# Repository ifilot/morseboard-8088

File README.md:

## MorseBoard 8088

**A single-board computer built around the Intel 8088 microprocessor.**

The name **MorseBoard** is a tribute to [Stephen P.
Morse](https://en.wikipedia.org/wiki/Stephen_P._Morse), the lead architect of
the Intel 8086 microprocessor — the foundational design on which the 8088 is
based. His work played a pivotal role in shaping early x86 computing.

## Board Layout

The 8088's 20-bit address bus allows access to **1 MiB** of addressable memory,
divided into:

- **512 KiB of RAM** in the lower memory segment  
- **512 KiB of ROM** in the upper memory segment  

Address/data multiplexing is handled using **74HCT573 latches**.  
Serial communication is enabled via a **TL16C550 UART** and a **MAX232** level
shifter.

Eight LEDs are connected to **I/O port `0x00`** using a **74HCT273 register**,
providing simple visual output.

A **7.3728 MHz CAN oscillator** is used to drive both the 8088 and the serial
interface. Because of this frequency, you must use the **8088-2** variant, which
supports higher clock rates.

## Design Files

- **PCB layout**: `pcb/morseboard-8088`  
- **Firmware source**: `src/uartboard`  

Assembly is done using the [NASM assembler](https://www.nasm.us/), available via
common Linux package managers (e.g., Ubuntu). A `Makefile` is provided for
convenience.

To flash the ROM, the recommended tool is the [PICO-SST39SF0x0
programmer](https://github.com/ifilot/pico-sst39sf0x0-programmer).

## Assembly instructions

To assemble the source code of the ROM, follow the instructions below. Make sure
you have installed the proper toolchain.

``` bash
sudo apt install nasm make
```

Go to the folder and run `make`

```bash
cd src/uartboard
make
```
Flash the resulting `rom.bin` onto the SST39SF040 chip.

## Test Board

In addition to the full-featured board with UART support, a **CPU test board**
is available under `pcb/cpu-testboard`. This board is designed to validate 8088
chips — particularly useful given the unreliability of some second-hand CPUs,
since they are no longer in production.

## License

### Hardware

The hardware design files for the MorseBoard 8088 are licensed under the  
**CERN Open Hardware License v2 - Strongly Reciprocal (CERN-OHL-S-2.0)**.  
You are free to use, modify, and distribute the hardware under the terms of this
license.  
More info: [CERN-OHL-S-2.0](https://ohwr.org/project/cernohl/wikis/Documents/CERN-OHL-version-2)

### Software

The firmware and software source code is licensed under the  
**GNU General Public License v3.0 (GPLv3)**.  
You are free to use, share, and modify the code as long as derivative works
remain under the same license.  
More info: [GPLv3 License](https://www.gnu.org/licenses/gpl-3.0.html)

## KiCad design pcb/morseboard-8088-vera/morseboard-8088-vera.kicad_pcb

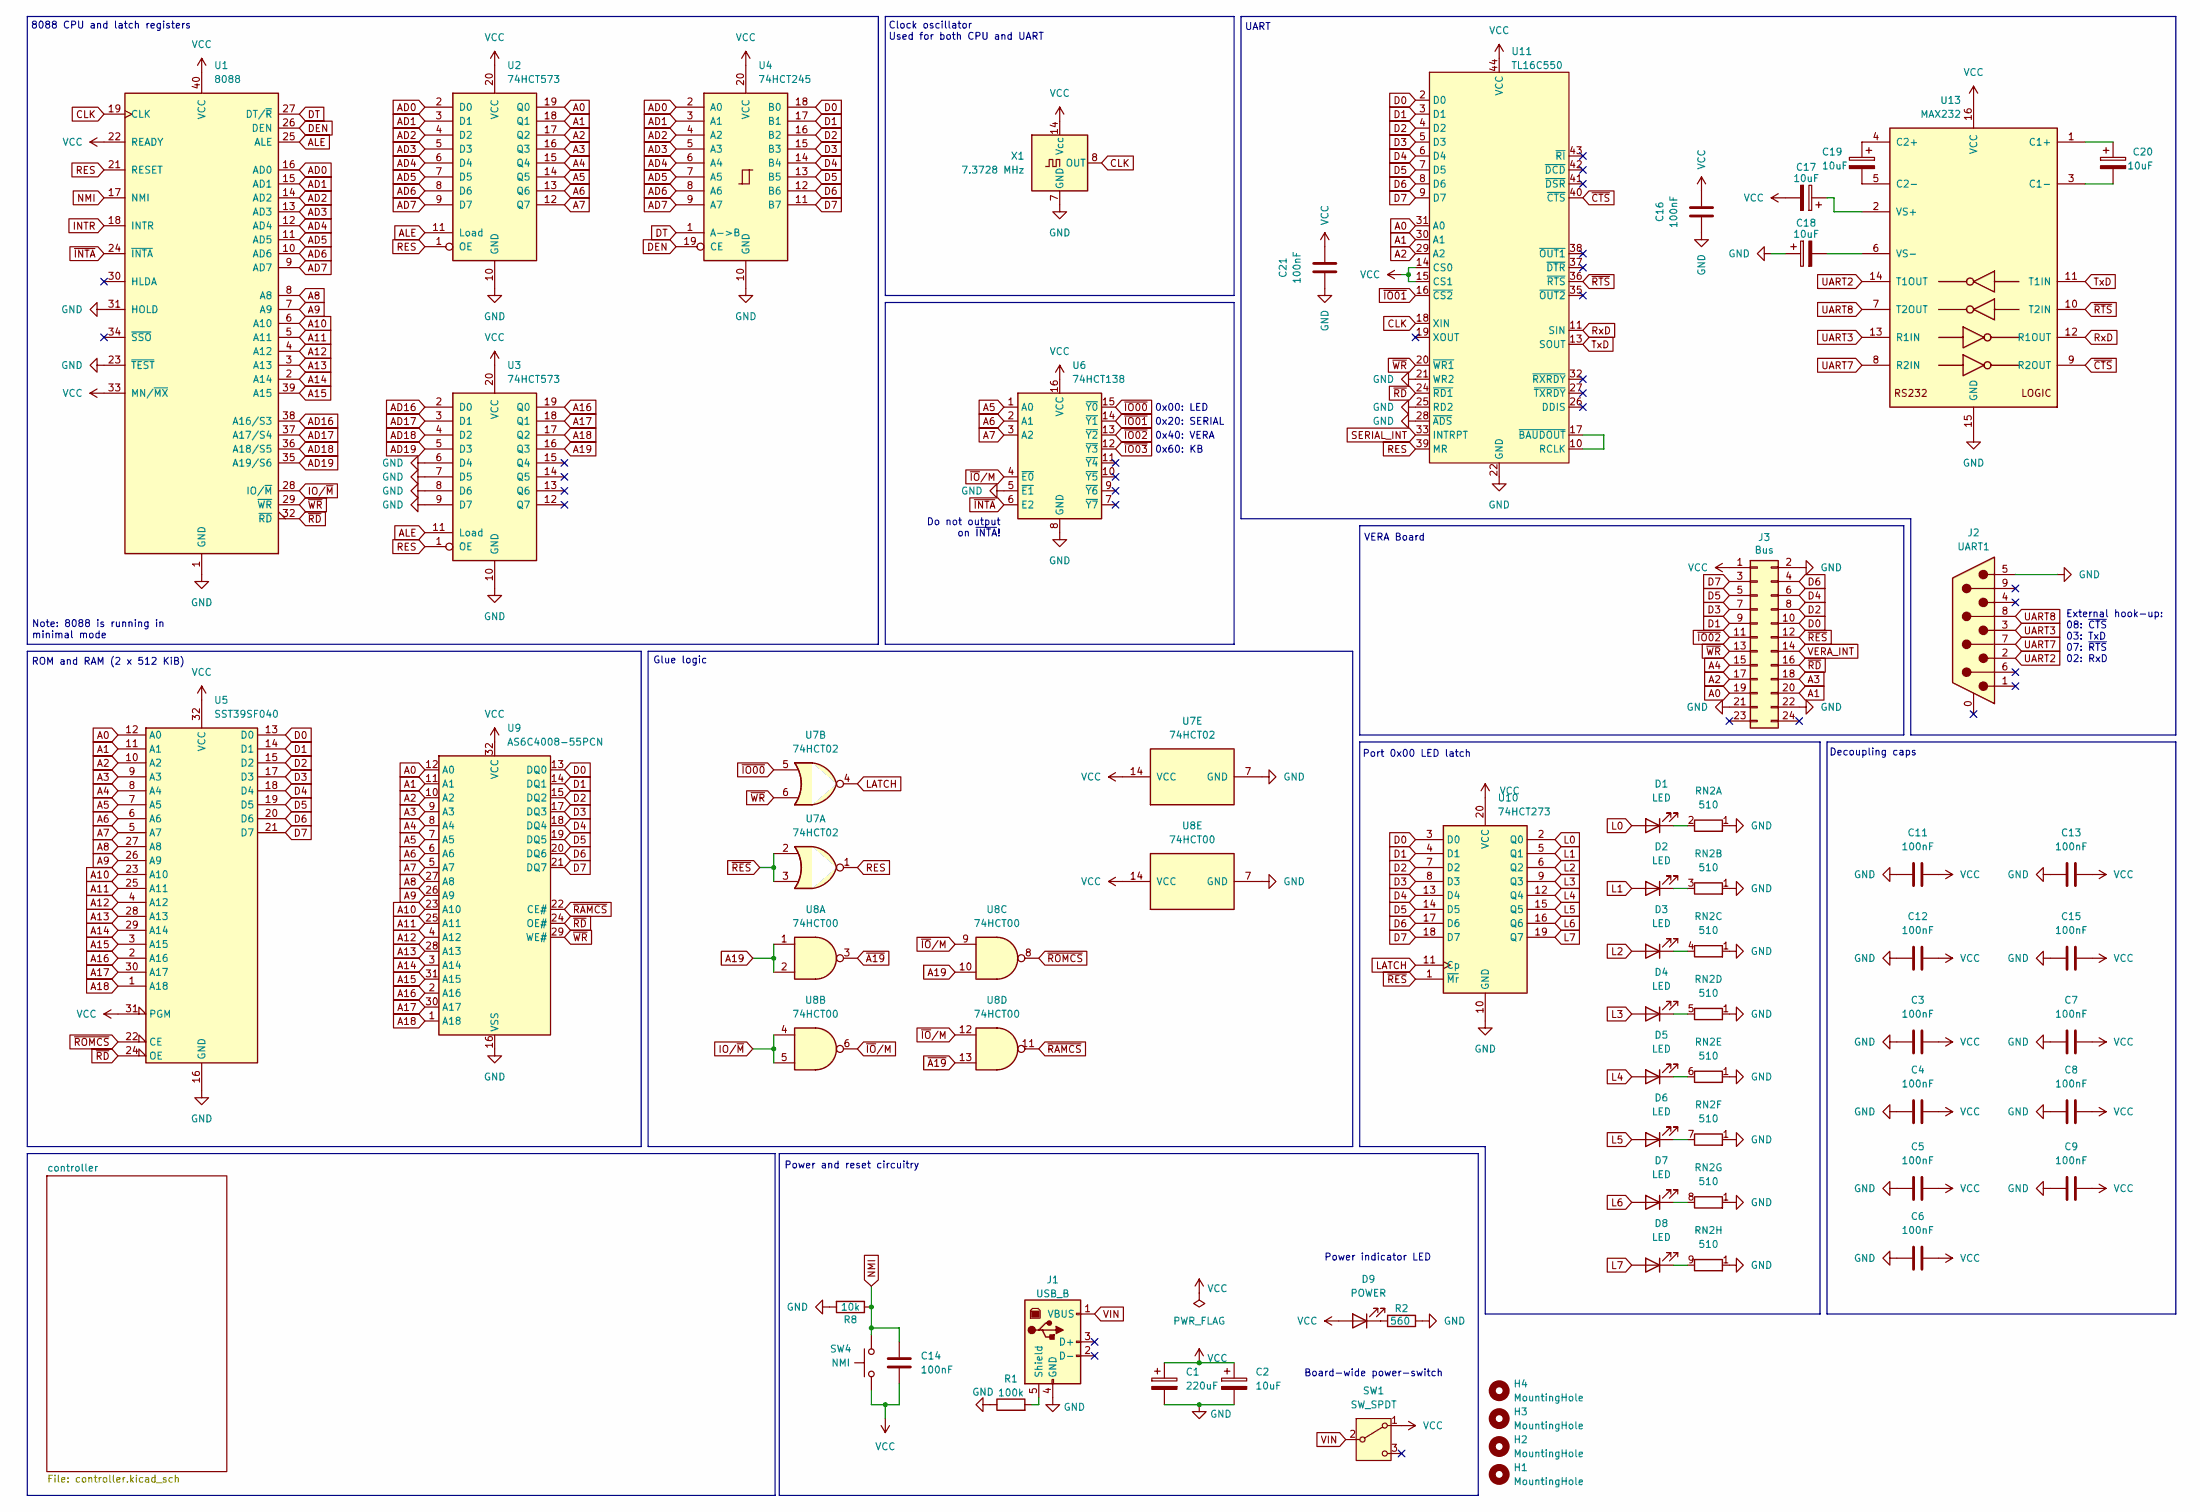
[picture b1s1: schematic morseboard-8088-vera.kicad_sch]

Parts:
C1: 220uF; CP_Radial_D6.3mm_P2.50mm
C2, C17, C18, C19, C20: 10uF; CP_Radial_D5.0mm_P2.50mm
C3, C4, C5, C6, C7, C8, C9, C11, C12, C13, C14, C15, C16, C21: 100nF; C_Disc_D5.0mm_W2.5mm_P5.00mm
D1, D2, D3, D4, D5, D6, D7, D8: LED; LED_D5.0mm
D9: POWER; LED_D5.0mm
H1, H2, H3, H4: MountingHole; MountingHole_3.2mm_M3_DIN965
J1: USB_B; USB_B_OST_USB-B1HSxx_Horizontal
J2: UART1; DSUB-9_Pins_Horizontal_P2.77x2.84mm_EdgePinOffset4.94mm_Hou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
J3: Bus; veraboard
R1: 100k; R_Axial_DIN0207_L6.3mm_D2.5mm_P7.62mm_Horizontal
R2: 560; R_Axial_DIN0207_L6.3mm_D2.5mm_P7.62mm_Horizontal
R8: 10k; R_Axial_DIN0207_L6.3mm_D2.5mm_P7.62mm_Horizontal
RN2: 510; R_Array_SIP9
SW1: SW_SPDT; power_switch
SW4: NMI; SW_PUSH_6mm
U1: 8088; DIP-40_W15.24mm_Socket
U2, U3: 74HCT573; DIP-20_W7.62mm_Socket
U4: 74HCT245; DIP-20_W7.62mm_Socket
U5: SST39SF040; DIP_Socket-32_W11.9mm_W12.7mm_W15.24mm_W17.78mm_W18.5mm_3M_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
U6: 74HCT138; DIP-16_W7.62mm_Socket
U7: 74HCT02; DIP-14_W7.62mm_Socket
U8: 74HCT00; DIP-14_W7.62mm_Socket
U9: AS6C4008-55PCN; DIP-32_W15.24mm_Socket
U10: 74HCT273; DIP-20_W7.62mm_Socket
U11: TL16C550; PLCC-44_THT-Socket
U13: MAX232; DIP-16_W7.62mm_Socket
X1: 7.3728 MHz; Oscillator_DIP-14

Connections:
A0: J3.19, U2.19 (Q0), U5.12 (A0), U9.12 (A0), U11.31 (A0)
A1: J3.20, U2.18 (Q1), U5.11 (A1), U9.11 (A1), U11.30 (A1)
A2: J3.17, U2.17 (Q2), U5.10 (A2), U9.10 (A2), U11.29 (A2)
A3: J3.18, U2.16 (Q3), U5.9 (A3), U9.9 (A3)
A4: J3.15, U2.15 (Q4), U5.8 (A4), U9.8 (A4)
A5: U2.14 (Q5), U5.7 (A5), U6.1 (A0), U9.7 (A5)
A6: U2.13 (Q6), U5.6 (A6), U6.2 (A1), U9.6 (A6)
A7: U2.12 (Q7), U5.5 (A7), U6.3 (A2), U9.5 (A7)
A8: U1.8 (A8), U5.27 (A8), U9.27 (A8)
A9: U1.7 (A9), U5.26 (A9), U9.26 (A9)
A10: U1.6 (A10), U5.23 (A10), U9.23 (A10)
A11: U1.5 (A11), U5.25 (A11), U9.25 (A11)
A12: U1.4 (A12), U5.4 (A12), U9.4 (A12)
A13: U1.3 (A13), U5.28 (A13), U9.28 (A13)
A14: U1.2 (A14), U5.29 (A14), U9.3 (A14)
A15: U1.39 (A15), U5.3 (A15), U9.31 (A15)
A16: U3.19 (Q0), U5.2 (A16), U9.2 (A16)
A17: U3.18 (Q1), U5.30 (A17), U9.30 (A17)
A18: U3.17 (Q2), U5.1 (A18), U9.1 (A18)
A19: U3.16 (Q3), U8.1, U8.2, U8.10
AD0: U1.16 (AD0), U2.2 (D0), U4.2 (A0); also elsewhere on the board
AD1: U1.15 (AD1), U2.3 (D1), U4.3 (A1); also elsewhere on the board
AD2: U1.14 (AD2), U2.4 (D2), U4.4 (A2); also elsewhere on the board
AD3: U1.13 (AD3), U2.5 (D3), U4.5 (A3); also elsewhere on the board
AD4: U1.12 (AD4), U2.6 (D4), U4.6 (A4); also elsewhere on the board
AD5: U1.11 (AD5), U2.7 (D5), U4.7 (A5); also elsewhere on the board
AD6: U1.10 (AD6), U2.8 (D6), U4.8 (A6); also elsewhere on the board
AD7: U1.9 (AD7), U2.9 (D7), U4.9 (A7); also elsewhere on the board
AD16: U1.38 (A16/S3), U3.2 (D0)
AD17: U1.37 (A17/S4), U3.3 (D1)
AD18: U1.36 (A18/S5), U3.4 (D2)
AD19: U1.35 (A19/S6), U3.5 (D3)
ALE: U1.25 (ALE), U2.11 (Load), U3.11 (Load)
CLK: U1.19 (CLK), U11.18 (XIN), X1.8 (OUT)
D0: J3.10, U4.18 (B0), U5.13 (D0), U9.13 (DQ0), U10.3 (D0), U11.2 (D0)
D1: J3.9, U4.17 (B1), U5.14 (D1), U9.14 (DQ1), U10.4 (D1), U11.3 (D1)
D2: J3.8, U4.16 (B2), U5.15 (D2), U9.15 (DQ2), U10.7 (D2), U11.4 (D2)
D3: J3.7, U4.15 (B3), U5.17 (D3), U9.17 (DQ3), U10.8 (D3), U11.5 (D3)
D4: J3.6, U4.14 (B4), U5.18 (D4), U9.18 (DQ4), U10.13 (D4), U11.6 (D4)
D5: J3.5, U4.13 (B5), U5.19 (D5), U9.19 (DQ5), U10.14 (D5), U11.7 (D5)
D6: J3.4, U4.12 (B6), U5.20 (D6), U9.20 (DQ6), U10.17 (D6), U11.8 (D6)
D7: J3.3, U4.11 (B7), U5.21 (D7), U9.21 (DQ7), U10.18 (D7), U11.9 (D7)
DEN: U1.26 (DEN), U4.19 (CE)
DT: U1.27 (DT/~R), U4.1 (A->B)
GND: C1.2, C2.2, C3.2, C4.2, C5.2, C6.2, C7.2, C8.2, C9.2, C11.2, C12.2, C13.2, C15.2, C16.2, C18.1, C21.2, J1.4 (GND), J2.5, J3.2, J3.21, J3.22, R1.1, R2.1, R8.2, RN2.1 (R1), U1.1 (GND), U1.20 (GND), U1.23 (~TEST), U1.31 (HOLD), U2.10 (GND), U3.6 (D4), U3.7 (D5), U3.8 (D6), U3.9 (D7), U3.10 (GND), U4.10 (GND), U5.16 (GND), U6.5 (~E1), U6.8 (GND), U7.7 (GND), U8.7 (GND), U9.16 (VSS), U10.10 (GND), U11.21 (WR2), U11.22 (GND), U11.25 (RD2), U11.28 (~ADS), U13.15 (GND), X1.7 (GND); also elsewhere on the board
INTR: U1.18 (INTR); also elsewhere on the board
IO/~M: U1.28 (IO/~M), U8.4, U8.5
L0: D1.2 (A), U10.2 (Q0)
L1: D2.2 (A), U10.5 (Q1)
L2: D3.2 (A), U10.6 (Q2)
L3: D4.2 (A), U10.9 (Q3)
L4: D5.2 (A), U10.12 (Q4)
L5: D6.2 (A), U10.15 (Q5)
L6: D7.2 (A), U10.16 (Q6)
L7: D8.2 (A), U10.19 (Q7)
LATCH: U7.4, U10.11 (Cp)
NMI: C14.1, R8.1, SW4.2, U1.17 (NMI)
unnamed: D1.1 (K), RN2.2 (R1.2)
unnamed: D2.1 (K), RN2.3 (R2.2)
unnamed: D3.1 (K), RN2.4 (R3.2)
unnamed: D4.1 (K), RN2.5 (R4.2)
unnamed: D5.1 (K), RN2.6 (R5.2)
unnamed: D6.1 (K), RN2.7 (R6.2)
unnamed: D7.1 (K), RN2.8 (R7.2)
unnamed: D8.1 (K), RN2.9 (R8.2)
unnamed: D9.1 (K), R2.2
unnamed: J1.5 (Shield), R1.2
unnamed: U11.10 (RCLK), U11.17 (~BAUDOUT)
unnamed: C20.1, U13.1 (C1+)
unnamed: C20.2, U13.3 (C1-)
unnamed: C19.1, U13.4 (C2+)
unnamed: C19.2, U13.5 (C2-)
unnamed: C17.1, U13.2 (VS+)
unnamed: C18.2, U13.6 (VS-)
RES: U1.21 (RESET), U2.1 (OE), U3.1 (OE), U7.1, U11.39 (MR)
RxD: U11.11 (SIN), U13.12 (R1OUT)
SERIAL_INT: U11.33 (INTRPT); also elsewhere on the board
TxD: U11.13 (SOUT), U13.11 (T1IN)
UART2: J2.2, U13.14 (T1OUT)
UART3: J2.3, U13.13 (R1IN)
UART7: J2.7, U13.8 (R2IN)
UART8: J2.8, U13.7 (T2OUT)
VCC: C1.1, C2.1, C3.1, C4.1, C5.1, C6.1, C7.1, C8.1, C9.1, C11.1, C12.1, C13.1, C14.2, C15.1, C16.1, C17.2, C21.1, D9.2 (A), J3.1, SW1.1 (A), SW4.1, U1.22 (READY), U1.33 (MN/~MX), U1.40 (VCC), U2.20 (VCC), U3.20 (VCC), U4.20 (VCC), U5.31 (PGM), U5.32 (VCC), U6.16 (VCC), U7.14 (VCC), U8.14 (VCC), U9.32 (VCC), U10.20 (VCC), U11.14 (CS0), U11.15 (CS1), U11.44 (VCC), U13.16 (VCC), X1.14 (Vcc); also elsewhere on the board
VERA_INT: J3.14; also elsewhere on the board
VIN: J1.1 (VBUS), SW1.2 (B)
~A19: U8.3, U8.13
~CTS: U11.40 (~CTS), U13.9 (R2OUT)
~INTA: U1.24 (~INTA), U6.6 (E2); also elsewhere on the board
~IO00: U6.15 (~Y0), U7.5
~IO01: U6.14 (~Y1), U11.16 (~CS2)
~IO02: J3.11, U6.13 (~Y2)
~IO03: U6.12 (~Y3); also elsewhere on the board
~IO/M: U6.4 (~E0), U8.6, U8.9, U8.12
~RAMCS: U8.11, U9.22 (CE#)
~RD: J3.16, U1.32 (~RD), U5.24 (OE), U9.24 (OE#), U11.24 (~RD1)
~RES: J3.12, U7.2, U7.3, U10.1 (~Mr); also elsewhere on the board
~ROMCS: U5.22 (CE), U8.8
~RTS: U11.36 (~RTS), U13.10 (T2IN)
~WR: J3.13, U1.29 (~WR), U7.6, U9.29 (WE#), U11.20 (~WR1)

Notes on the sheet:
Decoupling caps
0x20: SERIAL
Port 0x00 LED latch
Board-wide power-switch
8088 CPU and latch registers
Power and reset circuitry
Do not output on ~{INTA}!
UART
Power indicator LED
VERA Board
Glue logic
0x00: LED
ROM and RAM (2 x 512 KiB)
0x40: VERA
External hook-up: 08: ~{CTS} 03: TxD 07: ~{RTS} 02: RxD
Clock oscillator Used for both CPU and UART
0x60: KB
Note: 8088 is running in minimal mode

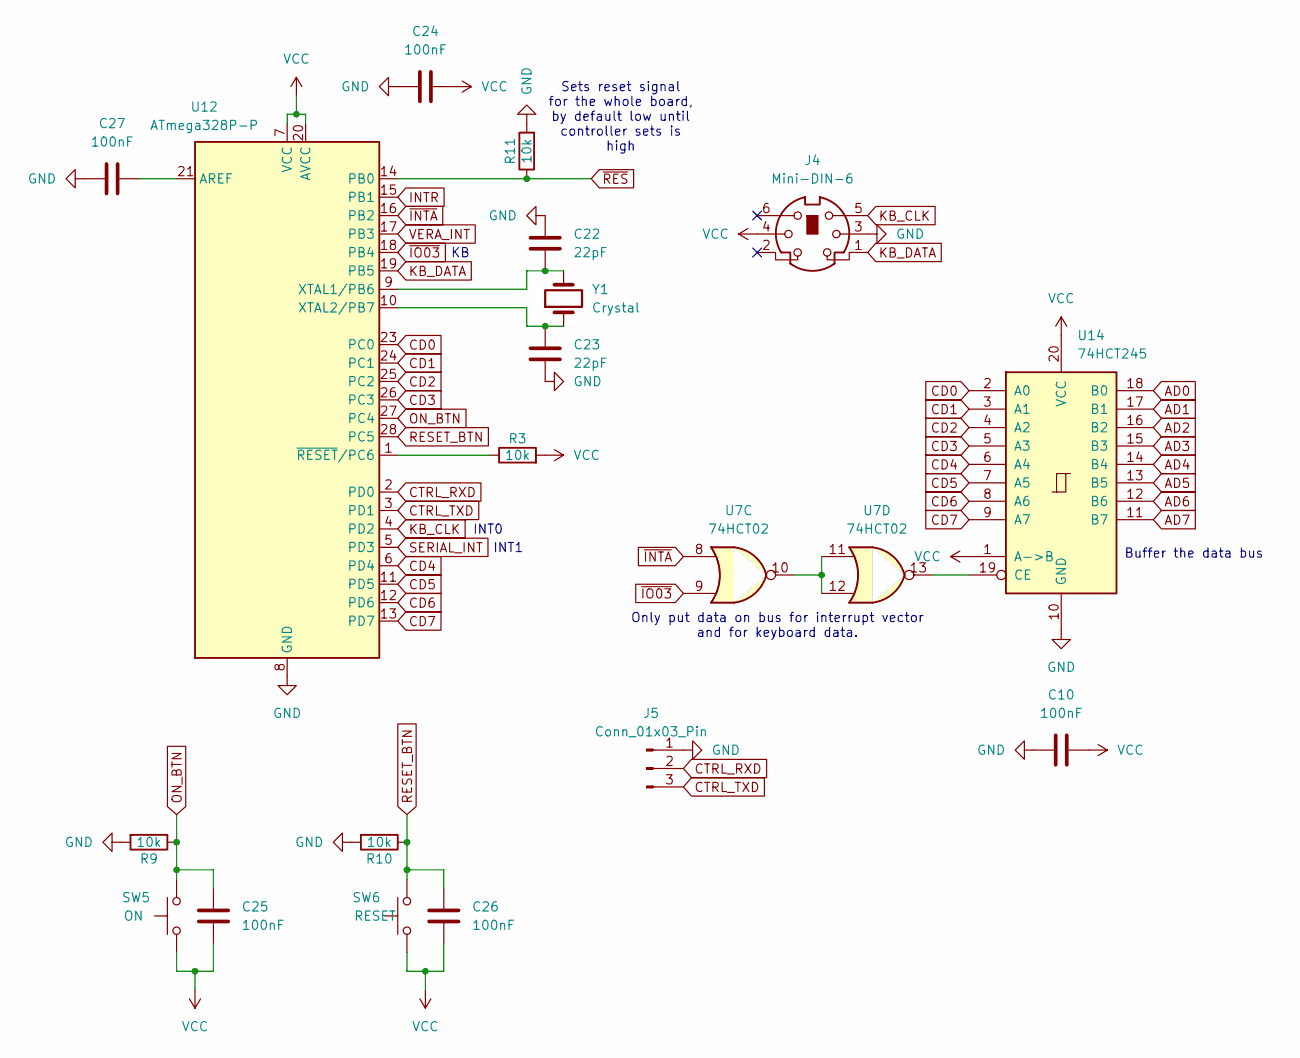
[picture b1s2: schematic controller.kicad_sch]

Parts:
C10, C24, C25, C26, C27: 100nF; C_Disc_D5.0mm_W2.5mm_P5.00mm
C22, C23: 22pF; C_Disc_D5.0mm_W2.5mm_P5.00mm
J4: Mini-DIN-6; J_Mini-DIN-6
J5: Conn_01x03_Pin; PinHeader_1x03_P2.54mm_Vertical
R3, R9, R10, R11: 10k; R_Axial_DIN0207_L6.3mm_D2.5mm_P7.62mm_Horizontal
SW5: ON; SW_PUSH_6mm
SW6: RESET; SW_PUSH_6mm
U7: 74HCT02; DIP-14_W7.62mm_Socket
U12: ATmega328P-P; DIP-28_W7.62mm_Socket
U14: 74HCT245; DIP-20_W7.62mm_Socket
Y1: Crystal; Crystal_HC49-4H_Vertical

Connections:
AD0: U14.18 (B0); also elsewhere on the board
AD1: U14.17 (B1); also elsewhere on the board
AD2: U14.16 (B2); also elsewhere on the board
AD3: U14.15 (B3); also elsewhere on the board
AD4: U14.14 (B4); also elsewhere on the board
AD5: U14.13 (B5); also elsewhere on the board
AD6: U14.12 (B6); also elsewhere on the board
AD7: U14.11 (B7); also elsewhere on the board
CD0: U12.23 (PC0), U14.2 (A0)
CD1: U12.24 (PC1), U14.3 (A1)
CD2: U12.25 (PC2), U14.4 (A2)
CD3: U12.26 (PC3), U14.5 (A3)
CD4: U12.6 (PD4), U14.6 (A4)
CD5: U12.11 (PD5), U14.7 (A5)
CD6: U12.12 (PD6), U14.8 (A6)
CD7: U12.13 (PD7), U14.9 (A7)
CTRL_RXD: J5.2, U12.2 (PD0)
CTRL_TXD: J5.3, U12.3 (PD1)
GND: C10.2, C22.1, C23.2, C24.2, C27.2, J4.3, J5.1, R9.2, R10.2, R11.2, U12.8 (GND), U12.22 (GND), U14.10 (GND); also elsewhere on the board
INTR: U12.15 (PB1); also elsewhere on the board
KB_CLK: J4.5, U12.4 (PD2)
KB_DATA: J4.1, U12.19 (PB5)
unnamed: U7.10, U7.11, U7.12
unnamed: C27.1, U12.21 (AREF)
unnamed: C22.2, U12.9 (XTAL1/PB6), Y1.2
unnamed: C23.1, U12.10 (XTAL2/PB7), Y1.1
unnamed: R3.1, U12.1 (~RESET/PC6)
unnamed: U7.13, U14.19 (CE)
ON_BTN: C25.1, R9.1, SW5.2, U12.27 (PC4)
RESET_BTN: C26.1, R10.1, SW6.2, U12.28 (PC5)
SERIAL_INT: U12.5 (PD3); also elsewhere on the board
VCC: C10.1, C24.1, C25.2, C26.2, J4.4, R3.2, SW5.1, SW6.1, U12.7 (VCC), U12.20 (AVCC), U14.1 (A->B), U14.20 (VCC); also elsewhere on the board
VERA_INT: U12.17 (PB3); also elsewhere on the board
~INTA: U7.8, U12.16 (PB2); also elsewhere on the board
~IO03: U7.9, U12.18 (PB4); also elsewhere on the board
~RES: R11.1, U12.14 (PB0); also elsewhere on the board

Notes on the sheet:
Only put data on bus for interrupt vector and for keyboard data.
INT0
Sets reset signal for the whole board, by default low until controller sets is high
Buffer the data bus
INT1

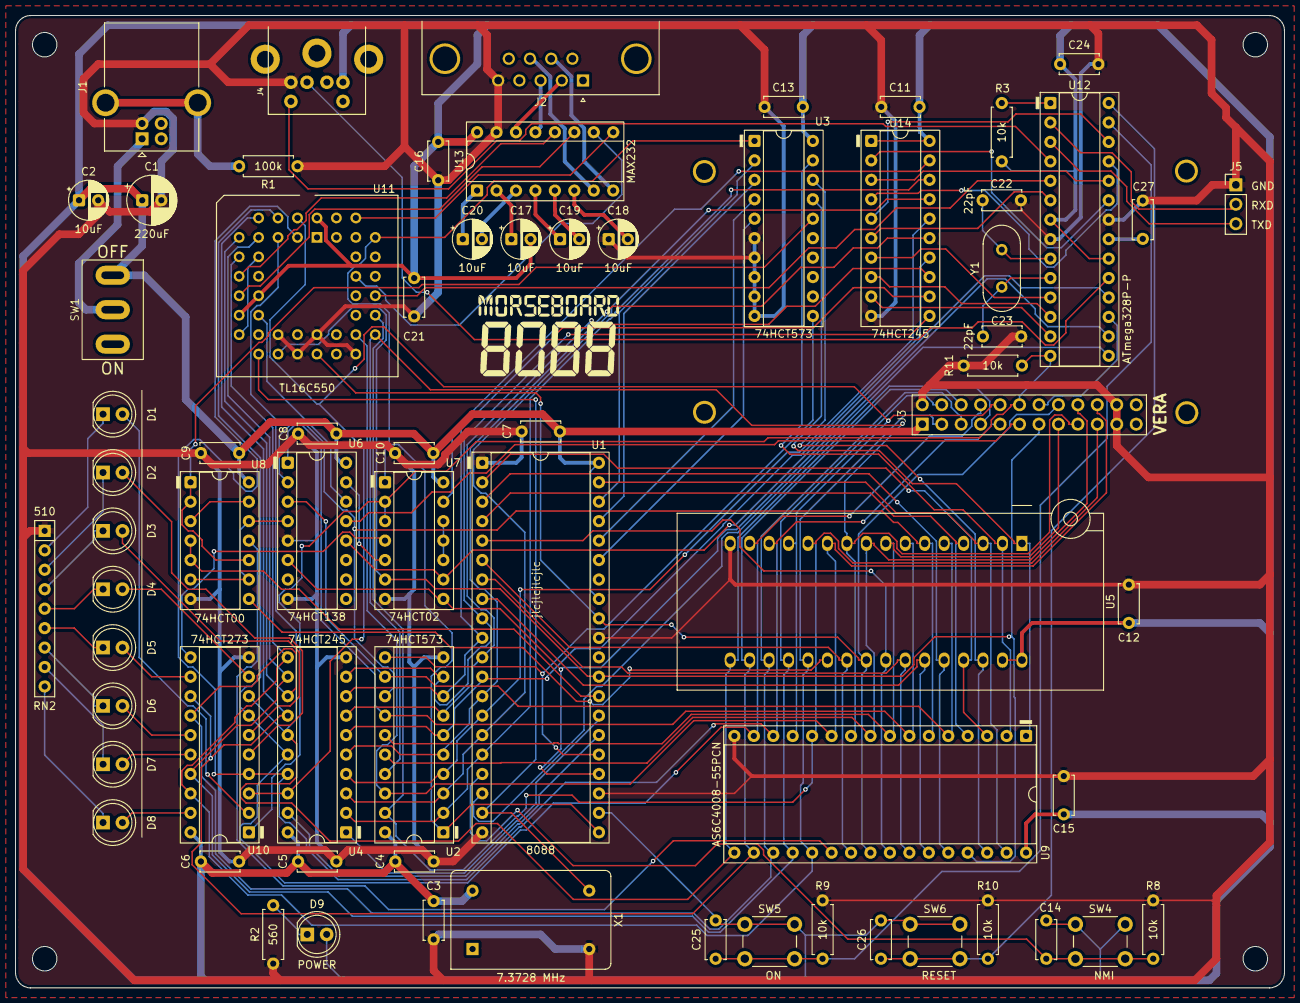
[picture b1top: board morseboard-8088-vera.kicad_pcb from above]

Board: 2 copper layers, 165.7 x 127.0 mm, 74 parts (0 on the bottom side), 119 nets.

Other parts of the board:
G001: LOGO; morseboard-logo-12h

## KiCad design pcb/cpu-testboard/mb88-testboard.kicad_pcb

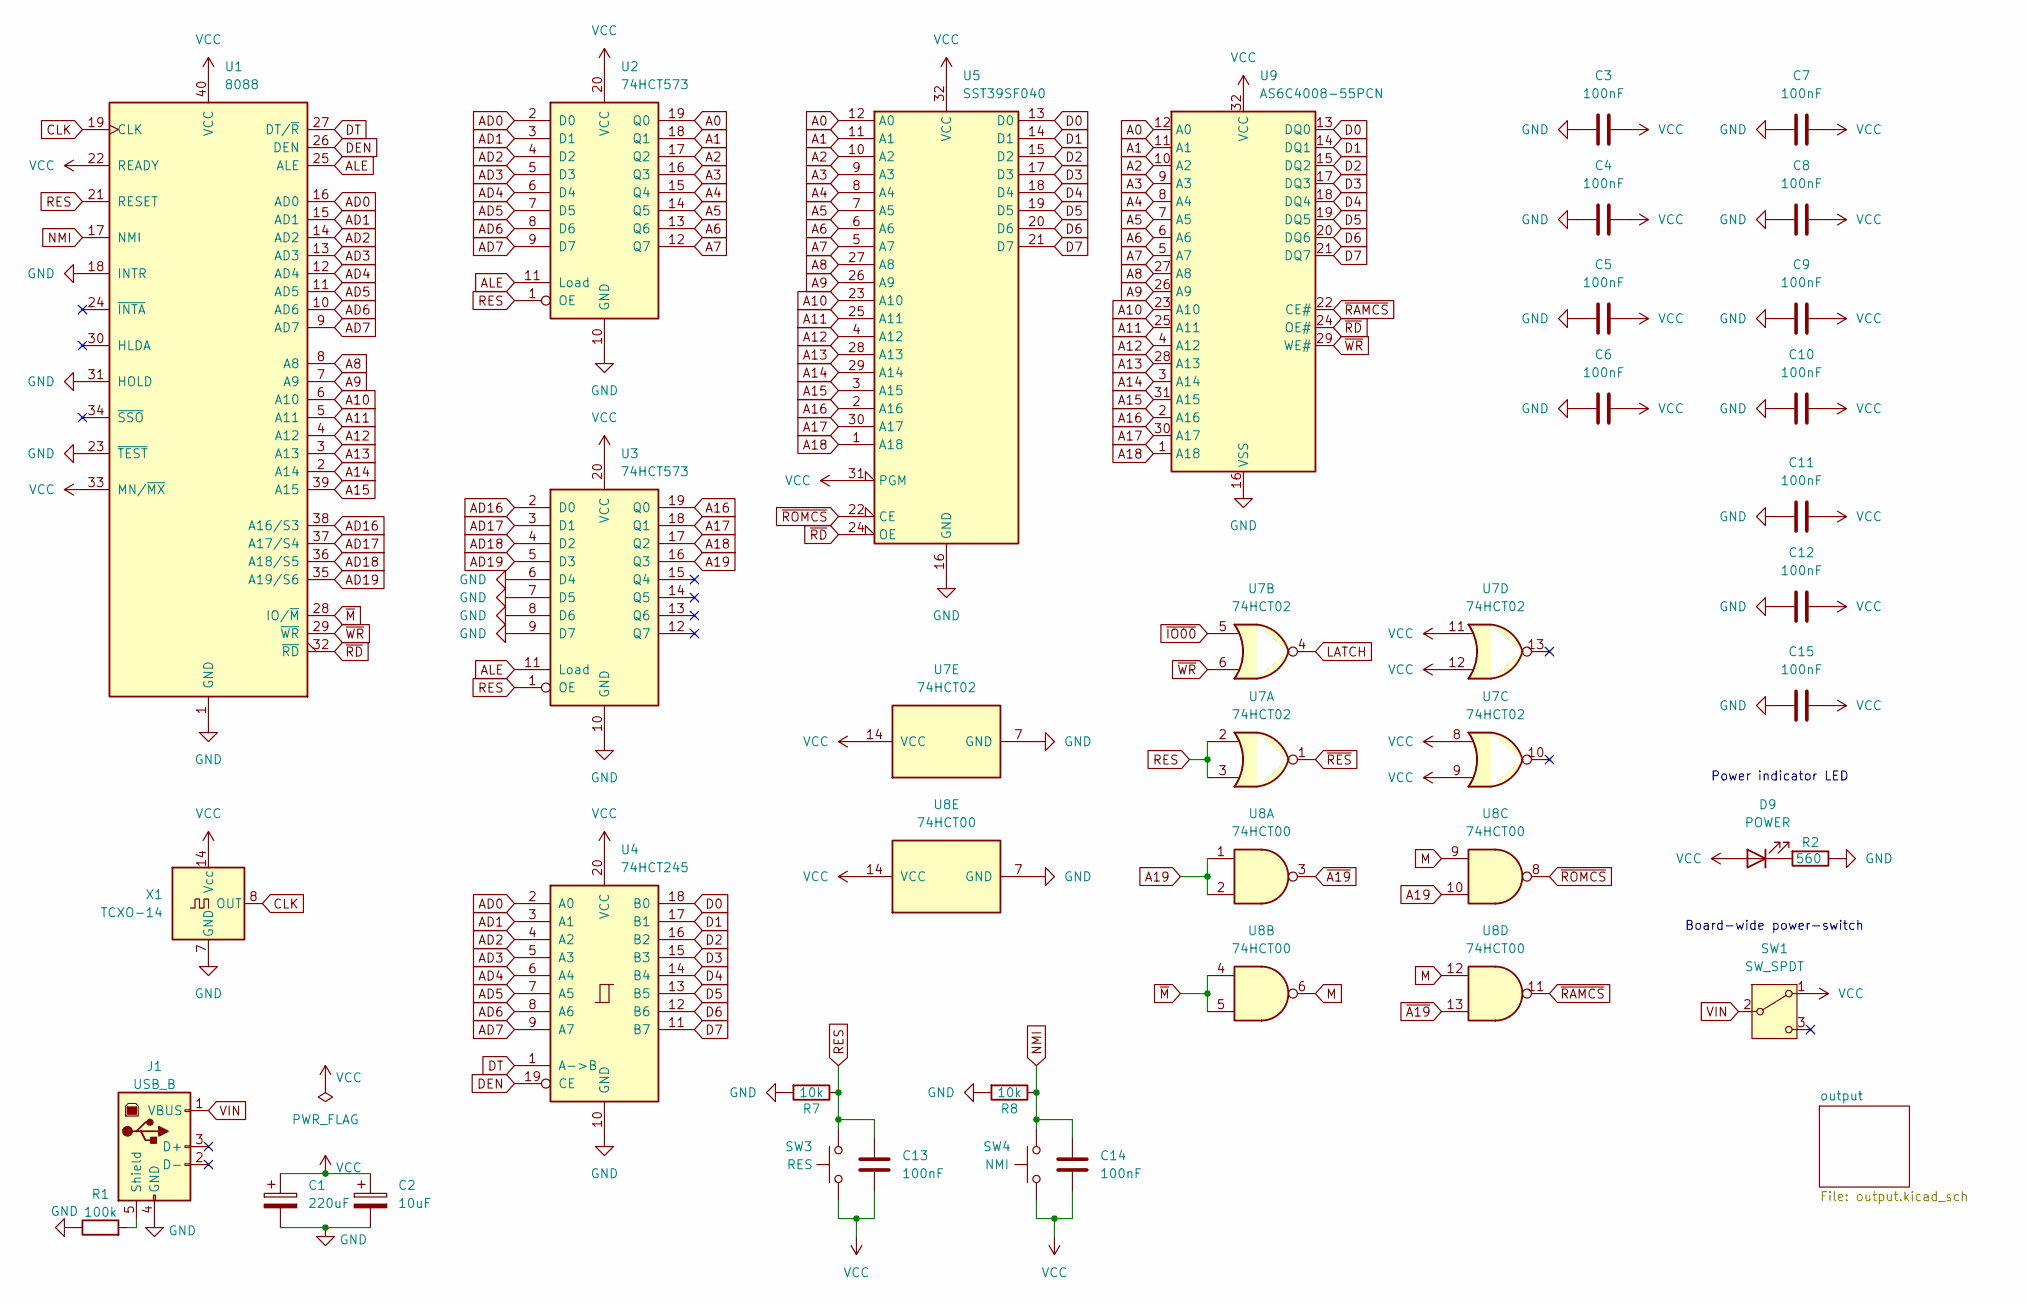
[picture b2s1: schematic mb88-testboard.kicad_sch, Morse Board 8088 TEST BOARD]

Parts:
C1: 220uF; CP_Radial_D6.3mm_P2.50mm
C2: 10uF; CP_Radial_D5.0mm_P2.50mm
C3, C4, C5, C6, C7, C8, C9, C10, C11, C12, C13, C14, C15: 100nF; C_Disc_D5.0mm_W2.5mm_P5.00mm
D9: POWER; LED_D5.0mm
J1: USB_B; USB_B_OST_USB-B1HSxx_Horizontal
R1: 100k; R_Axial_DIN0207_L6.3mm_D2.5mm_P7.62mm_Horizontal
R2: 560; R_Axial_DIN0207_L6.3mm_D2.5mm_P7.62mm_Horizontal
R7, R8: 10k; R_Axial_DIN0207_L6.3mm_D2.5mm_P7.62mm_Horizontal
SW1: SW_SPDT; power_switch
SW3: RES; SW_PUSH_6mm
SW4: NMI; SW_PUSH_6mm
U1: 8088; DIP-40_W15.24mm_Socket
U2, U3: 74HCT573; DIP-20_W7.62mm_Socket
U4: 74HCT245; DIP-20_W7.62mm_Socket
U5: SST39SF040; DIP_Socket-32_W11.9_W12.7_W15.24_W17.78_W18.5_3M_232-1285-0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
U7: 74HCT02; DIP-14_W7.62mm_Socket
U8: 74HCT00; DIP-14_W7.62mm_Socket
U9: AS6C4008-55PCN; DIP-32_W15.24mm_Socket
X1: TCXO-14; Oscillator_DIP-14

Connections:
A0: U2.19 (Q0), U5.12 (A0), U9.12 (A0); also elsewhere on the board
A1: U2.18 (Q1), U5.11 (A1), U9.11 (A1); also elsewhere on the board
A2: U2.17 (Q2), U5.10 (A2), U9.10 (A2); also elsewhere on the board
A3: U2.16 (Q3), U5.9 (A3), U9.9 (A3); also elsewhere on the board
A4: U2.15 (Q4), U5.8 (A4), U9.8 (A4); also elsewhere on the board
A5: U2.14 (Q5), U5.7 (A5), U9.7 (A5); also elsewhere on the board
A6: U2.13 (Q6), U5.6 (A6), U9.6 (A6); also elsewhere on the board
A7: U2.12 (Q7), U5.5 (A7), U9.5 (A7); also elsewhere on the board
A8: U1.8 (A8), U5.27 (A8), U9.27 (A8); also elsewhere on the board
A9: U1.7 (A9), U5.26 (A9), U9.26 (A9); also elsewhere on the board
A10: U1.6 (A10), U5.23 (A10), U9.23 (A10); also elsewhere on the board
A11: U1.5 (A11), U5.25 (A11), U9.25 (A11); also elsewhere on the board
A12: U1.4 (A12), U5.4 (A12), U9.4 (A12); also elsewhere on the board
A13: U1.3 (A13), U5.28 (A13), U9.28 (A13); also elsewhere on the board
A14: U1.2 (A14), U5.29 (A14), U9.3 (A14); also elsewhere on the board
A15: U1.39 (A15), U5.3 (A15), U9.31 (A15); also elsewhere on the board
A16: U3.19 (Q0), U5.2 (A16), U9.2 (A16); also elsewhere on the board
A17: U3.18 (Q1), U5.30 (A17), U9.30 (A17); also elsewhere on the board
A18: U3.17 (Q2), U5.1 (A18), U9.1 (A18); also elsewhere on the board
A19: U3.16 (Q3), U8.1, U8.2, U8.10; also elsewhere on the board
AD0: U1.16 (AD0), U2.2 (D0), U4.2 (A0)
AD1: U1.15 (AD1), U2.3 (D1), U4.3 (A1)
AD2: U1.14 (AD2), U2.4 (D2), U4.4 (A2)
AD3: U1.13 (AD3), U2.5 (D3), U4.5 (A3)
AD4: U1.12 (AD4), U2.6 (D4), U4.6 (A4)
AD5: U1.11 (AD5), U2.7 (D5), U4.7 (A5)
AD6: U1.10 (AD6), U2.8 (D6), U4.8 (A6)
AD7: U1.9 (AD7), U2.9 (D7), U4.9 (A7)
AD16: U1.38 (A16/S3), U3.2 (D0)
AD17: U1.37 (A17/S4), U3.3 (D1)
AD18: U1.36 (A18/S5), U3.4 (D2)
AD19: U1.35 (A19/S6), U3.5 (D3)
ALE: U1.25 (ALE), U2.11 (Load), U3.11 (Load)
CLK: U1.19 (CLK), X1.8 (OUT); also elsewhere on the board
D0: U4.18 (B0), U5.13 (D0), U9.13 (DQ0); also elsewhere on the board
D1: U4.17 (B1), U5.14 (D1), U9.14 (DQ1); also elsewhere on the board
D2: U4.16 (B2), U5.15 (D2), U9.15 (DQ2); also elsewhere on the board
D3: U4.15 (B3), U5.17 (D3), U9.17 (DQ3); also elsewhere on the board
D4: U4.14 (B4), U5.18 (D4), U9.18 (DQ4); also elsewhere on the board
D5: U4.13 (B5), U5.19 (D5), U9.19 (DQ5); also elsewhere on the board
D6: U4.12 (B6), U5.20 (D6), U9.20 (DQ6); also elsewhere on the board
D7: U4.11 (B7), U5.21 (D7), U9.21 (DQ7); also elsewhere on the board
DEN: U1.26 (DEN), U4.19 (CE); also elsewhere on the board
DT: U1.27 (DT/~R), U4.1 (A->B)
GND: C1.2, C2.2, C3.2, C4.2, C5.2, C6.2, C7.2, C8.2, C9.2, C10.2, C11.2, C12.2, C15.2, J1.4 (GND), R1.1, R2.1, R7.2, R8.2, U1.1 (GND), U1.18 (INTR), U1.20 (GND), U1.23 (~TEST), U1.31 (HOLD), U2.10 (GND), U3.6 (D4), U3.7 (D5), U3.8 (D6), U3.9 (D7), U3.10 (GND), U4.10 (GND), U5.16 (GND), U7.7 (GND), U8.7 (GND), U9.16 (VSS), X1.7 (GND); also elsewhere on the board
LATCH: U7.4; also elsewhere on the board
M: U8.6, U8.9, U8.12
NMI: C14.1, R8.1, SW4.2, U1.17 (NMI)
unnamed: D9.1 (K), R2.2
unnamed: J1.5 (Shield), R1.2
RES: C13.1, R7.1, SW3.2, U1.21 (RESET), U2.1 (OE), U3.1 (OE), U7.2, U7.3; also elsewhere on the board
VCC: C1.1, C2.1, C3.1, C4.1, C5.1, C6.1, C7.1, C8.1, C9.1, C10.1, C11.1, C12.1, C13.2, C14.2, C15.1, D9.2 (A), SW1.1 (A), SW3.1, SW4.1, U1.22 (READY), U1.33 (MN/~MX), U1.40 (VCC), U2.20 (VCC), U3.20 (VCC), U4.20 (VCC), U5.31 (PGM), U5.32 (VCC), U7.8, U7.9, U7.11, U7.12, U7.14 (VCC), U8.14 (VCC), U9.32 (VCC), X1.14 (Vcc); also elsewhere on the board
VIN: J1.1 (VBUS), SW1.2 (B)
~A19: U8.3, U8.13
~IO00: U7.5; also elsewhere on the board
~M: U1.28 (IO/~M), U8.4, U8.5; also elsewhere on the board
~RAMCS: U8.11, U9.22 (CE#)
~RD: U1.32 (~RD), U5.24 (OE), U9.24 (OE#)
~RES: U7.1; also elsewhere on the board
~ROMCS: U5.22 (CE), U8.8
~WR: U1.29 (~WR), U7.6, U9.29 (WE#)

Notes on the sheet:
Board-wide power-switch
Power indicator LED

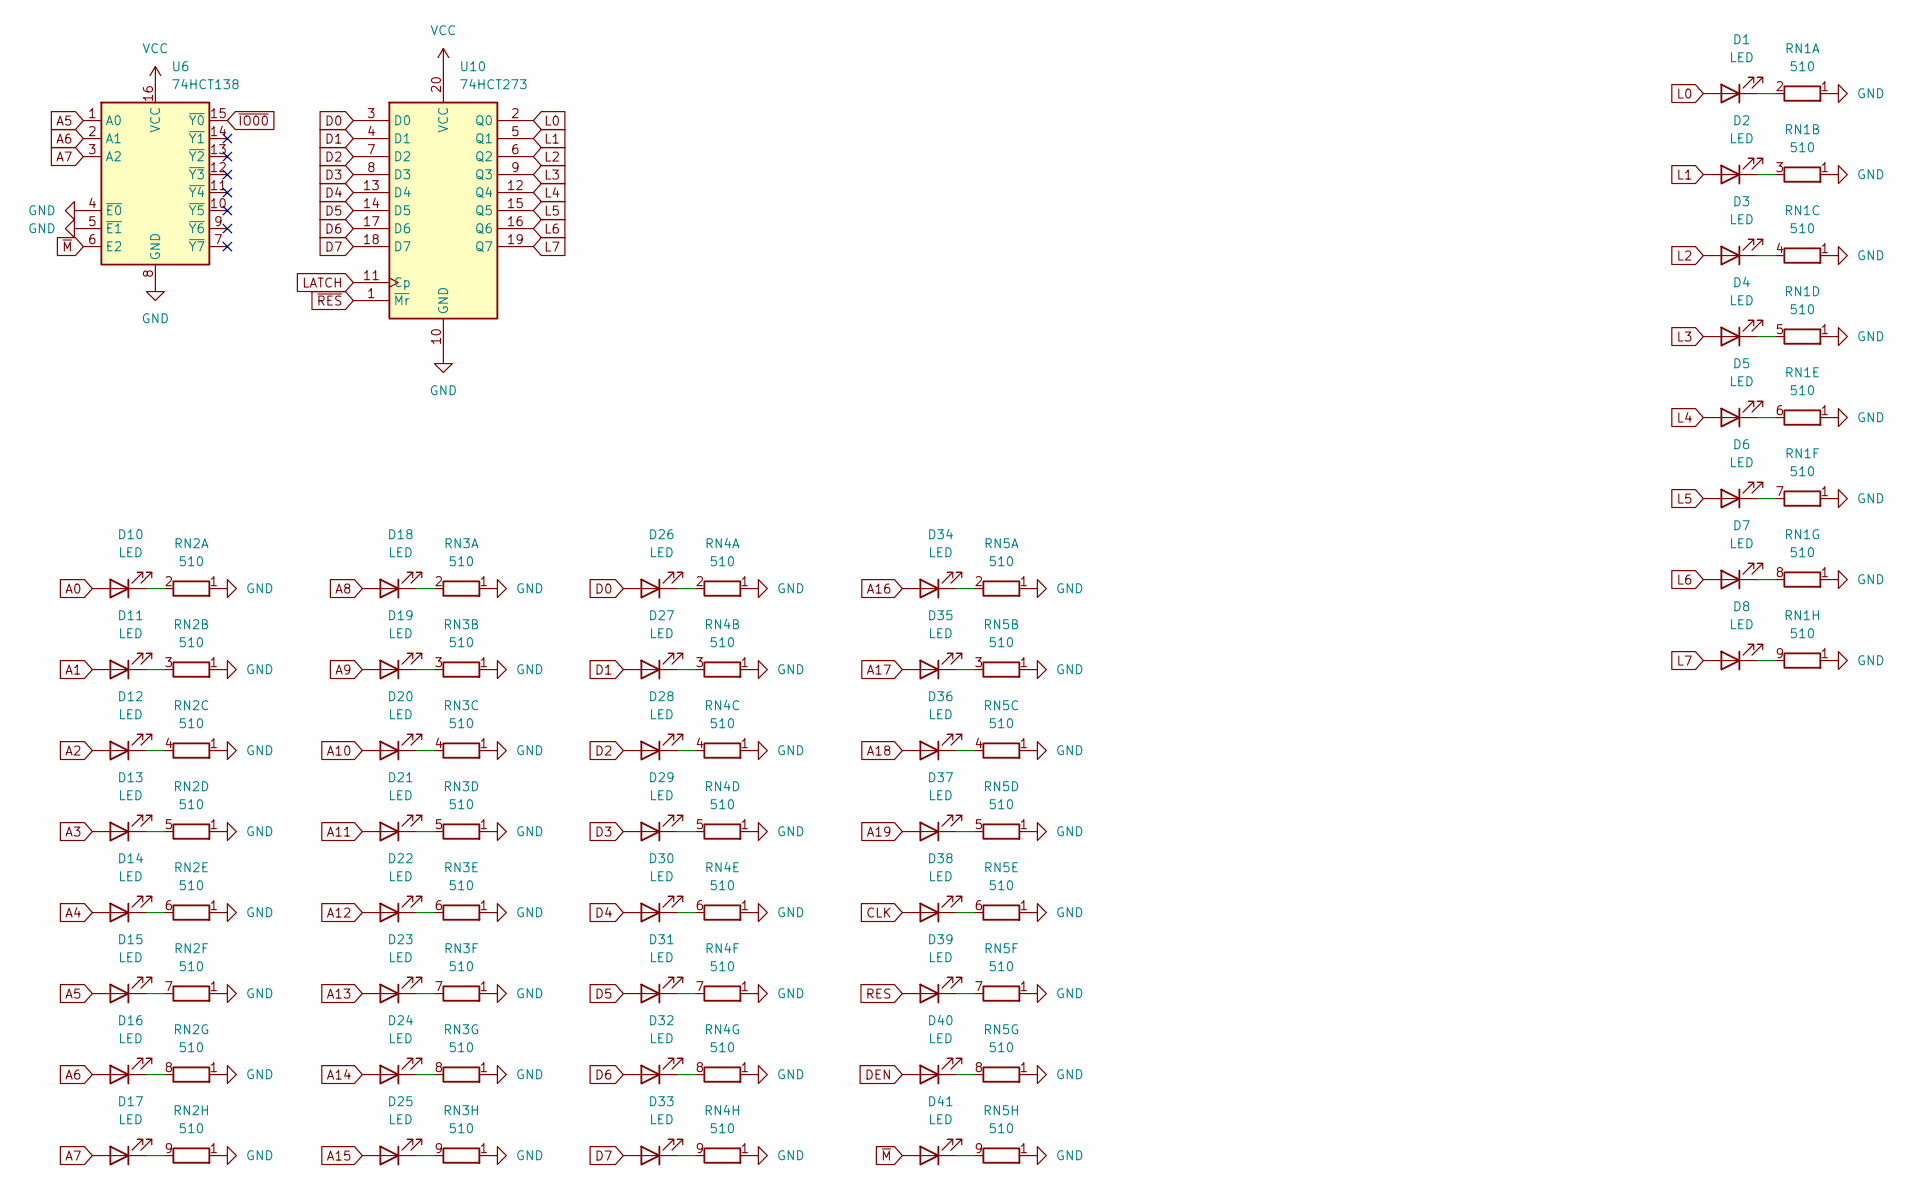
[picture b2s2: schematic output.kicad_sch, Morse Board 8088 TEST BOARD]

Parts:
D1, D2, D3, D4, D5, D6, D7, D8, D10, D11, D12, D13, D14, D15, D16, D17, D18, D19, D20, D21, D22, D23, D24, D25, D26, D27, D28, D29, D30, D31, D32, D33, D34, D35, D36, D37, D38, D39, D40, D41: LED; LED_D5.0mm
RN1, RN2, RN3, RN4, RN5: 510; R_Array_SIP9
U6: 74HCT138; DIP-16_W7.62mm_Socket
U10: 74HCT273; DIP-20_W7.62mm_Socket

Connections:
A0: D10.2 (A); also elsewhere on the board
A1: D11.2 (A); also elsewhere on the board
A2: D12.2 (A); also elsewhere on the board
A3: D13.2 (A); also elsewhere on the board
A4: D14.2 (A); also elsewhere on the board
A5: D15.2 (A), U6.1 (A0); also elsewhere on the board
A6: D16.2 (A), U6.2 (A1); also elsewhere on the board
A7: D17.2 (A), U6.3 (A2); also elsewhere on the board
A8: D18.2 (A); also elsewhere on the board
A9: D19.2 (A); also elsewhere on the board
A10: D20.2 (A); also elsewhere on the board
A11: D21.2 (A); also elsewhere on the board
A12: D22.2 (A); also elsewhere on the board
A13: D23.2 (A); also elsewhere on the board
A14: D24.2 (A); also elsewhere on the board
A15: D25.2 (A); also elsewhere on the board
A16: D34.2 (A); also elsewhere on the board
A17: D35.2 (A); also elsewhere on the board
A18: D36.2 (A); also elsewhere on the board
A19: D37.2 (A); also elsewhere on the board
CLK: D38.2 (A); also elsewhere on the board
D0: D26.2 (A), U10.3 (D0); also elsewhere on the board
D1: D27.2 (A), U10.4 (D1); also elsewhere on the board
D2: D28.2 (A), U10.7 (D2); also elsewhere on the board
D3: D29.2 (A), U10.8 (D3); also elsewhere on the board
D4: D30.2 (A), U10.13 (D4); also elsewhere on the board
D5: D31.2 (A), U10.14 (D5); also elsewhere on the board
D6: D32.2 (A), U10.17 (D6); also elsewhere on the board
D7: D33.2 (A), U10.18 (D7); also elsewhere on the board
DEN: D40.2 (A); also elsewhere on the board
GND: RN1.1 (R1), RN2.1 (R1), RN3.1 (R1), RN4.1 (R1), RN5.1 (R1), U6.4 (~E0), U6.5 (~E1), U6.8 (GND), U10.10 (GND); also elsewhere on the board
L0: D1.2 (A), U10.2 (Q0)
L1: D2.2 (A), U10.5 (Q1)
L2: D3.2 (A), U10.6 (Q2)
L3: D4.2 (A), U10.9 (Q3)
L4: D5.2 (A), U10.12 (Q4)
L5: D6.2 (A), U10.15 (Q5)
L6: D7.2 (A), U10.16 (Q6)
L7: D8.2 (A), U10.19 (Q7)
LATCH: U10.11 (Cp); also elsewhere on the board
unnamed: D1.1 (K), RN1.2 (R1.2)
unnamed: D2.1 (K), RN1.3 (R2.2)
unnamed: D3.1 (K), RN1.4 (R3.2)
unnamed: D4.1 (K), RN1.5 (R4.2)
unnamed: D5.1 (K), RN1.6 (R5.2)
unnamed: D6.1 (K), RN1.7 (R6.2)
unnamed: D7.1 (K), RN1.8 (R7.2)
unnamed: D8.1 (K), RN1.9 (R8.2)
unnamed: D10.1 (K), RN2.2 (R1.2)
unnamed: D11.1 (K), RN2.3 (R2.2)
unnamed: D12.1 (K), RN2.4 (R3.2)
unnamed: D13.1 (K), RN2.5 (R4.2)
unnamed: D14.1 (K), RN2.6 (R5.2)
unnamed: D15.1 (K), RN2.7 (R6.2)
unnamed: D16.1 (K), RN2.8 (R7.2)
unnamed: D17.1 (K), RN2.9 (R8.2)
unnamed: D18.1 (K), RN3.2 (R1.2)
unnamed: D19.1 (K), RN3.3 (R2.2)
unnamed: D20.1 (K), RN3.4 (R3.2)
unnamed: D21.1 (K), RN3.5 (R4.2)
unnamed: D22.1 (K), RN3.6 (R5.2)
unnamed: D23.1 (K), RN3.7 (R6.2)
unnamed: D24.1 (K), RN3.8 (R7.2)
unnamed: D25.1 (K), RN3.9 (R8.2)
unnamed: D26.1 (K), RN4.2 (R1.2)
unnamed: D27.1 (K), RN4.3 (R2.2)
unnamed: D28.1 (K), RN4.4 (R3.2)
unnamed: D29.1 (K), RN4.5 (R4.2)
unnamed: D30.1 (K), RN4.6 (R5.2)
unnamed: D31.1 (K), RN4.7 (R6.2)
unnamed: D32.1 (K), RN4.8 (R7.2)
unnamed: D33.1 (K), RN4.9 (R8.2)
unnamed: D34.1 (K), RN5.2 (R1.2)
unnamed: D35.1 (K), RN5.3 (R2.2)
unnamed: D36.1 (K), RN5.4 (R3.2)
unnamed: D37.1 (K), RN5.5 (R4.2)
unnamed: D38.1 (K), RN5.6 (R5.2)
unnamed: D39.1 (K), RN5.7 (R6.2)
unnamed: D40.1 (K), RN5.8 (R7.2)
unnamed: D41.1 (K), RN5.9 (R8.2)
RES: D39.2 (A); also elsewhere on the board
VCC: U6.16 (VCC), U10.20 (VCC); also elsewhere on the board
~IO00: U6.15 (~Y0); also elsewhere on the board
~M: D41.2 (A), U6.6 (E2); also elsewhere on the board
~RES: U10.1 (~Mr); also elsewhere on the board
